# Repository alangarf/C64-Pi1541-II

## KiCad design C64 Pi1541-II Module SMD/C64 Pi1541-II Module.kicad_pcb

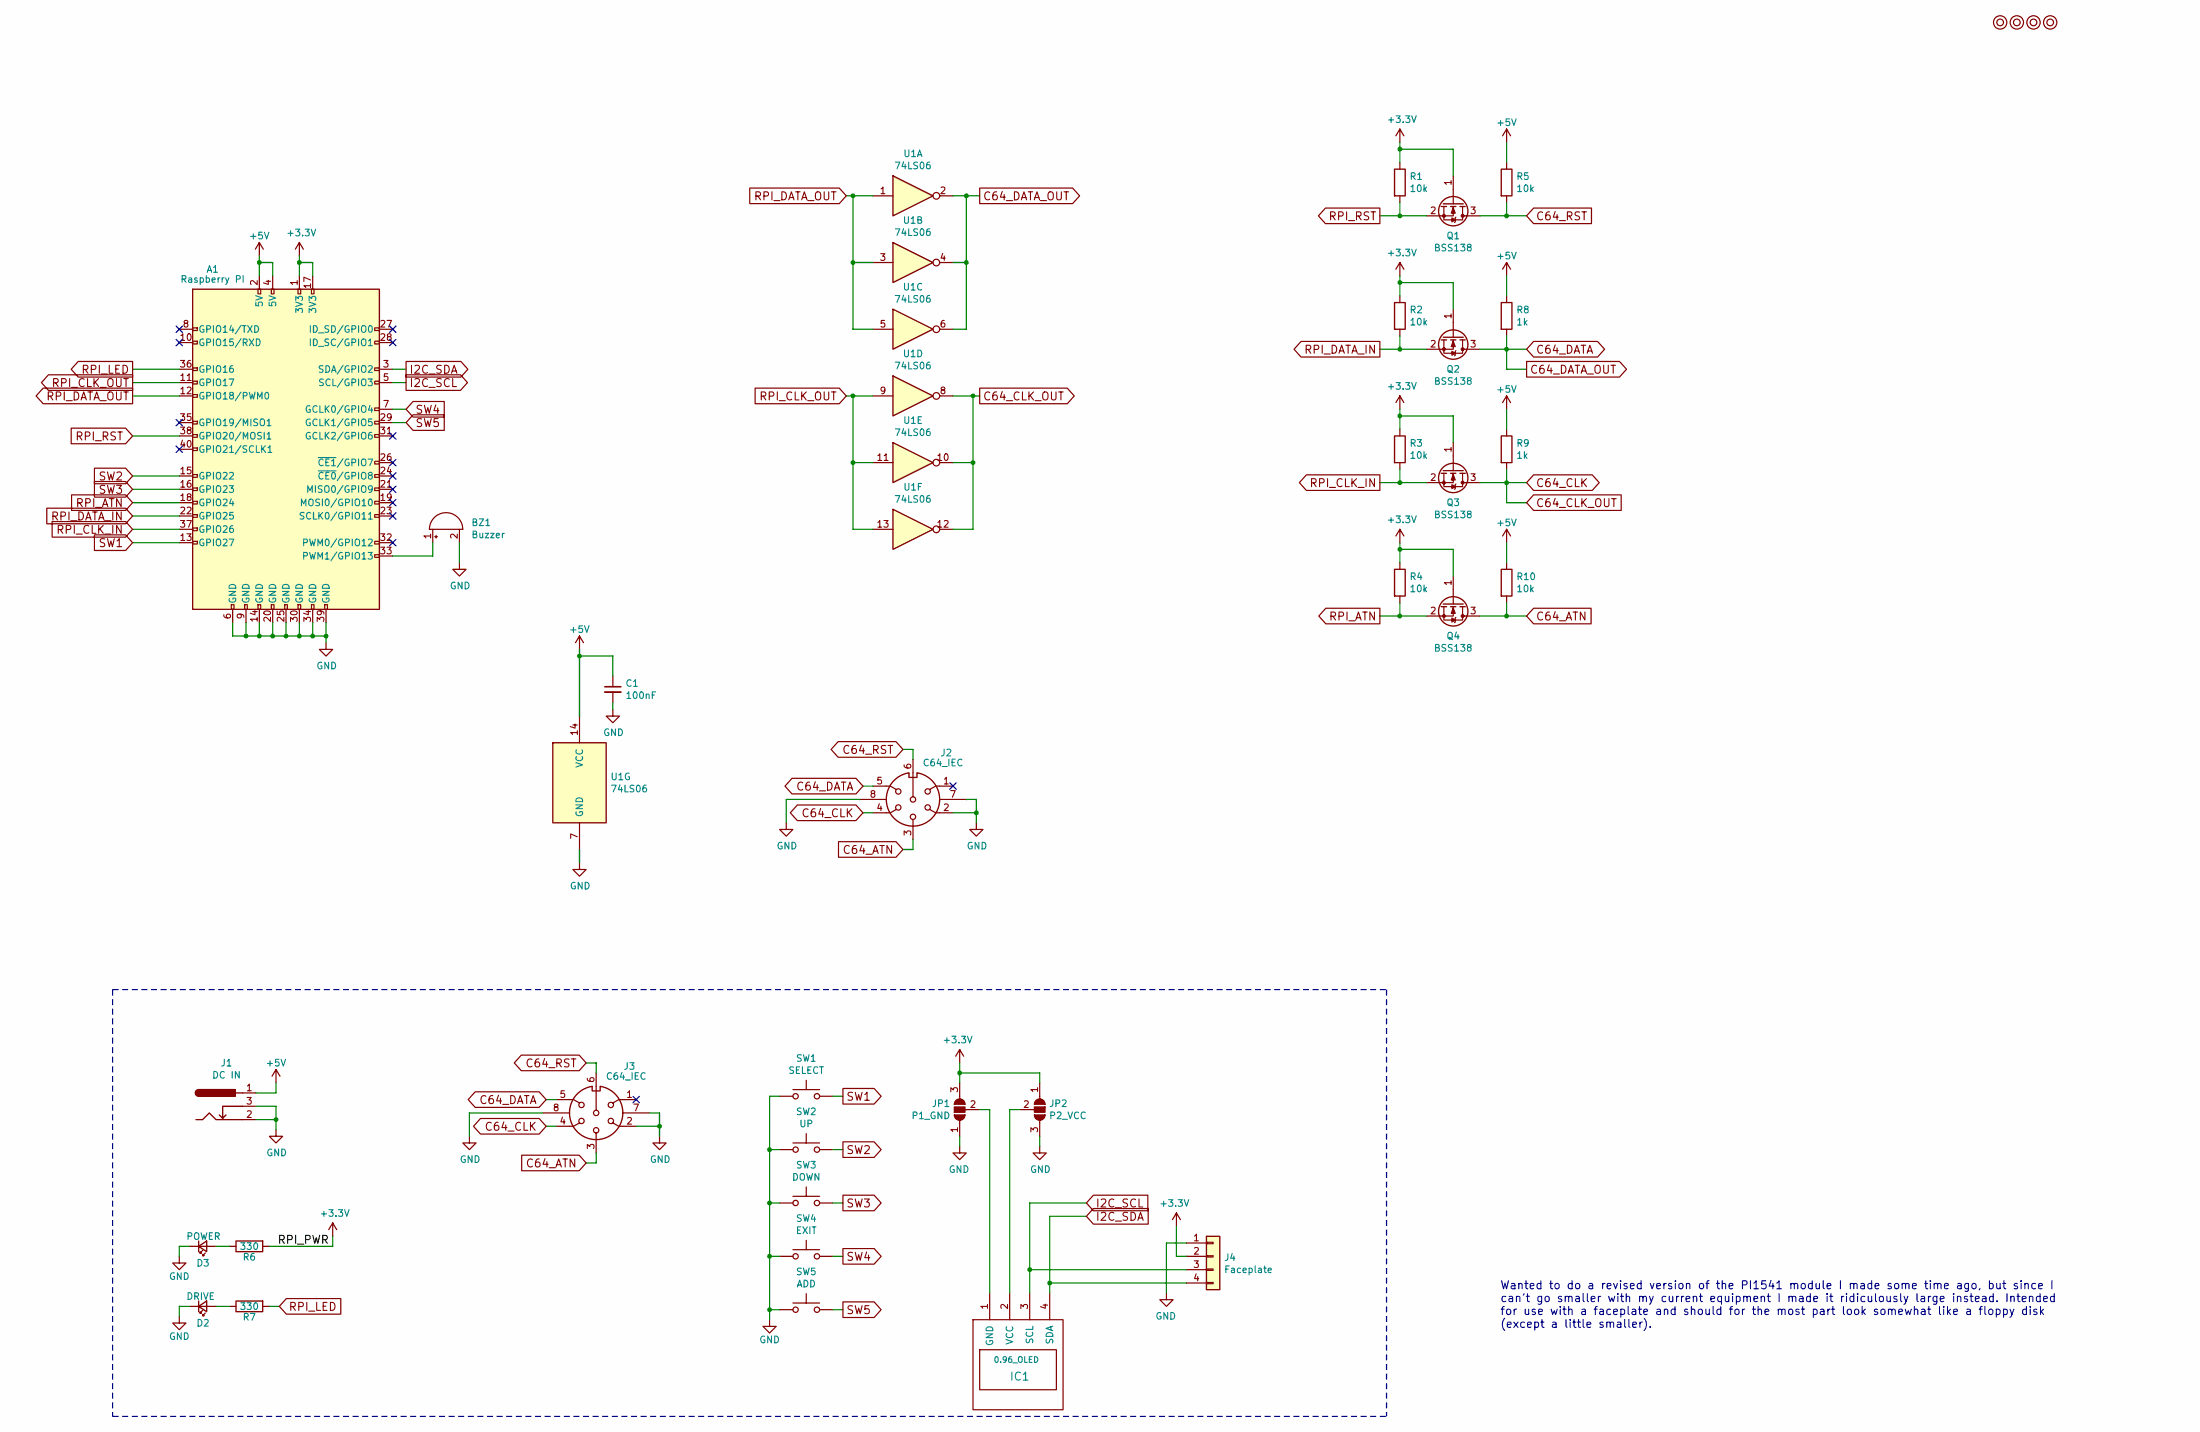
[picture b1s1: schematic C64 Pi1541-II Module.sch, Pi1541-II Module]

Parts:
A1: Raspberry PI; Raspberry_Pi_3B_Socketed_THT_FaceDown_MountingHoles
BZ1: Buzzer; Buzzer_12x9.5RM7.6
C1: 100nF; C_0805_2012Metric_Pad1.18x1.45mm_HandSolder
D2: DRIVE; LED_0805_2012Metric_Pad1.15x1.40mm_HandSolder
D3: POWER; LED_0805_2012Metric_Pad1.15x1.40mm_HandSolder
IC1: 0.96_OLED; 0.96_I2C_OLED
J1: DC IN; BarrelJack_Horizontal
J2, J3: C64_IEC
J4: Faceplate; PinHeader_1x04_P2.54mm_Vertical
JP1: P1_GND; OLED_SEL
JP2: P2_VCC; OLED_SEL
M1, M2, M3, M4: Mounting; M3
Q1, Q2, Q3, Q4: BSS138; SOT-23
R1, R2, R3, R4, R5, R10: 10k; R_0805_2012Metric_Pad1.20x1.40mm_HandSolder
R6, R7: 330; R_0805_2012Metric_Pad1.20x1.40mm_HandSolder
R8, R9: 1k; R_0805_2012Metric_Pad1.20x1.40mm_HandSolder
SW1: SELECT; SW_Tactile_SPST_Angled_PTS645Vx39-2LFS
SW2: UP; SW_Tactile_SPST_Angled_PTS645Vx39-2LFS
SW3: DOWN; SW_Tactile_SPST_Angled_PTS645Vx39-2LFS
SW4: EXIT; SW_Tactile_SPST_Angled_PTS645Vx39-2LFS
SW5: ADD; SW_Tactile_SPST_Angled_PTS645Vx39-2LFS
U1: 74LS06; SOIC-14_3.9x8.7mm_P1.27mm

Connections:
+3V3: A1.1 (3V3), A1.17 (3V3), J4.2, JP1.3 (B), JP2.1 (A), Q1.1 (G), Q2.1 (G), Q3.1 (G), Q4.1 (G), R1.1, R2.1, R3.1, R4.1, R6.2
+5V: A1.2 (5V), A1.4 (5V), C1.1, J1.1, R5.1, R8.1, R9.1, R10.1, U1.14 (VCC)
C64_ATN: J2.3, J3.3, Q4.3 (D), R10.2
C64_CLK: J2.4, J3.4, Q3.3 (D), R9.2, U1.8, U1.10, U1.12
C64_DATA: J2.5, J3.5, Q2.3 (D), R8.2, U1.2, U1.4, U1.6
C64_RST: J2.6, J3.6, Q1.3 (D), R5.2
GND: A1.6 (GND), A1.9 (GND), A1.14 (GND), A1.20 (GND), A1.25 (GND), A1.30 (GND), A1.34 (GND), A1.39 (GND), BZ1.2 (+), C1.2, D2.1 (K), D3.1 (K), J1.2, J1.3, J2.2, J2.7, J2.8, J3.2, J3.7, J3.8, J4.1, JP1.1 (A), JP2.3 (B), SW1.1, SW2.1, SW3.1, SW4.1, SW5.1, U1.7 (GND)
I2C_SCL: A1.5 (SCL/GPIO3), IC1.3 (SCL), J4.3
I2C_SDA: A1.3 (SDA/GPIO2), IC1.4 (SDA), J4.4
unnamed: A1.33 (PWM1/GPIO13), BZ1.1 (-)
unnamed: D2.2 (A), R7.1
unnamed: D3.2 (A), R6.1
unnamed: IC1.1 (GND), JP1.2 (C)
unnamed: IC1.2 (VCC), JP2.2 (C)
RPI_ATN: A1.18 (GPIO24), Q4.2 (S), R4.2
RPI_CLK_IN: A1.37 (GPIO26), Q3.2 (S), R3.2
RPI_CLK_OUT: A1.11 (GPIO17), U1.9, U1.11, U1.13
RPI_DATA_IN: A1.22 (GPIO25), Q2.2 (S), R2.2
RPI_DATA_OUT: A1.12 (GPIO18/PWM0), U1.1, U1.3, U1.5
RPI_LED: A1.36 (GPIO16), R7.2
RPI_RST: A1.38 (GPIO20/MOSI1), Q1.2 (S), R1.2
SW1: A1.13 (GPIO27), SW1.2
SW2: A1.15 (GPIO22), SW2.2
SW3: A1.16 (GPIO23), SW3.2
SW4: A1.7 (GCLK0/GPIO4), SW4.2
SW5: A1.29 (GCLK1/GPIO5), SW5.2

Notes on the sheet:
Wanted to do a revised version of the PI1541 module I made some time ago, but since I can't go smaller with my current equipment I made it ridiculously large instead. Intended for use with a faceplate and should for the most part look somewhat like a floppy disk (except a little smaller).

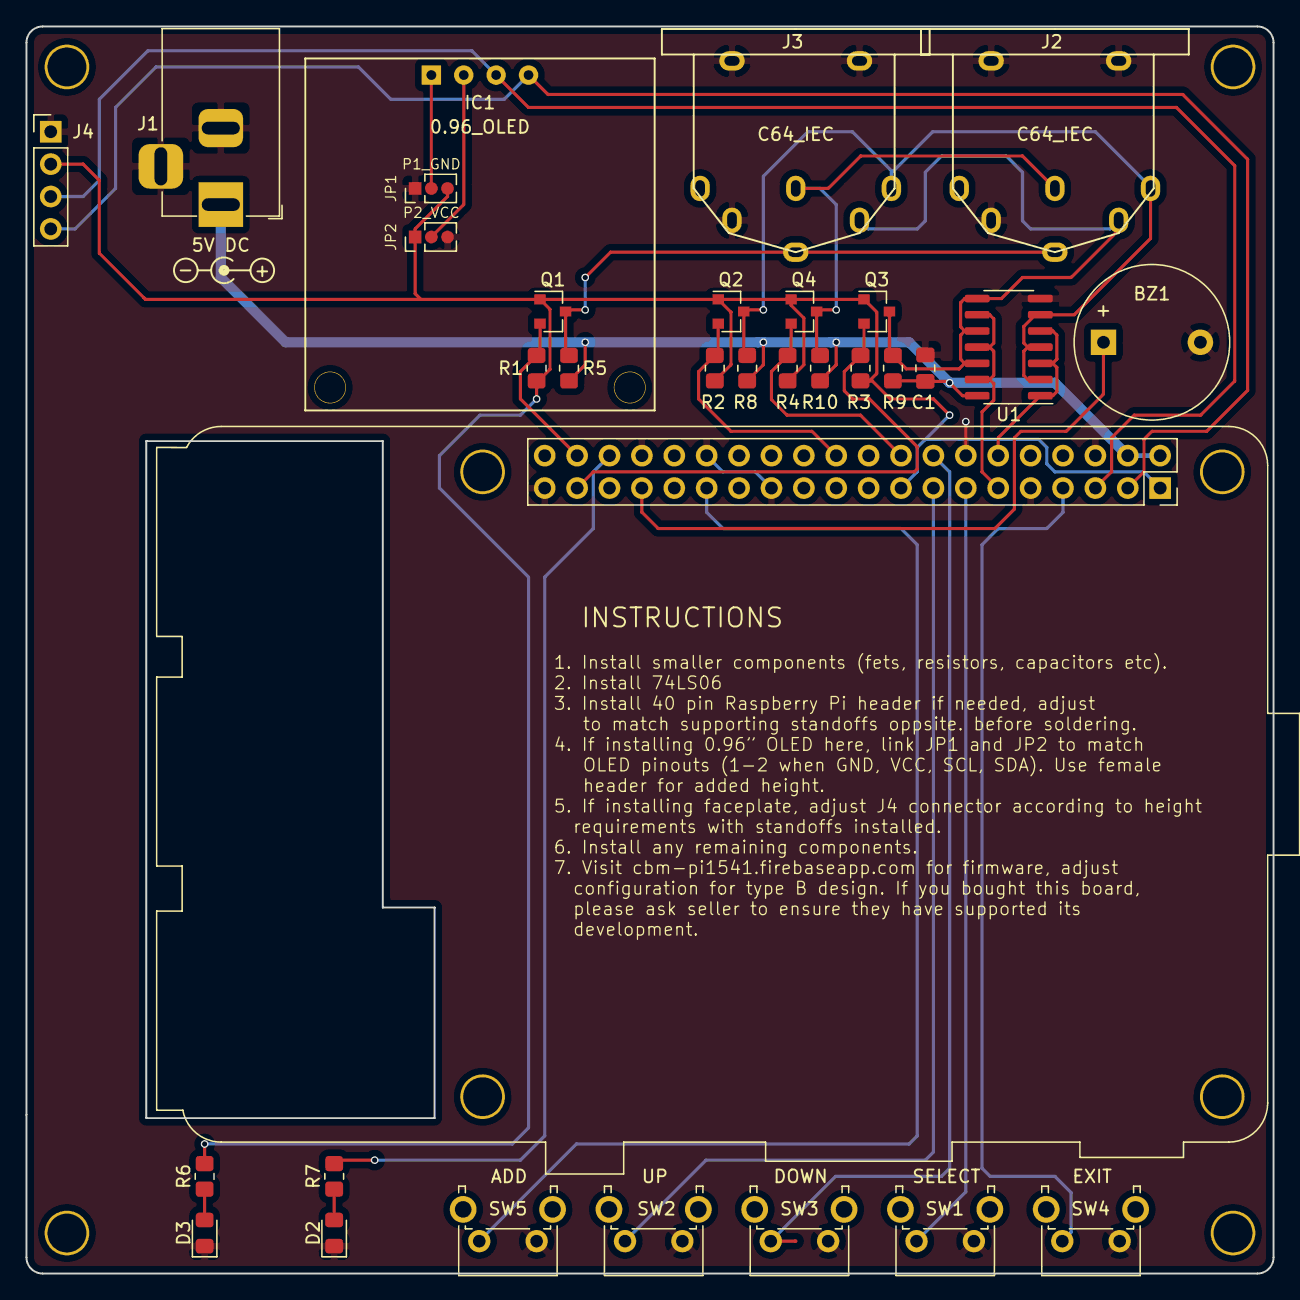
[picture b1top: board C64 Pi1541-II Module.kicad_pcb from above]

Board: 2 copper layers, 97.8 x 97.8 mm, 36 parts (0 on the bottom side), 26 nets.

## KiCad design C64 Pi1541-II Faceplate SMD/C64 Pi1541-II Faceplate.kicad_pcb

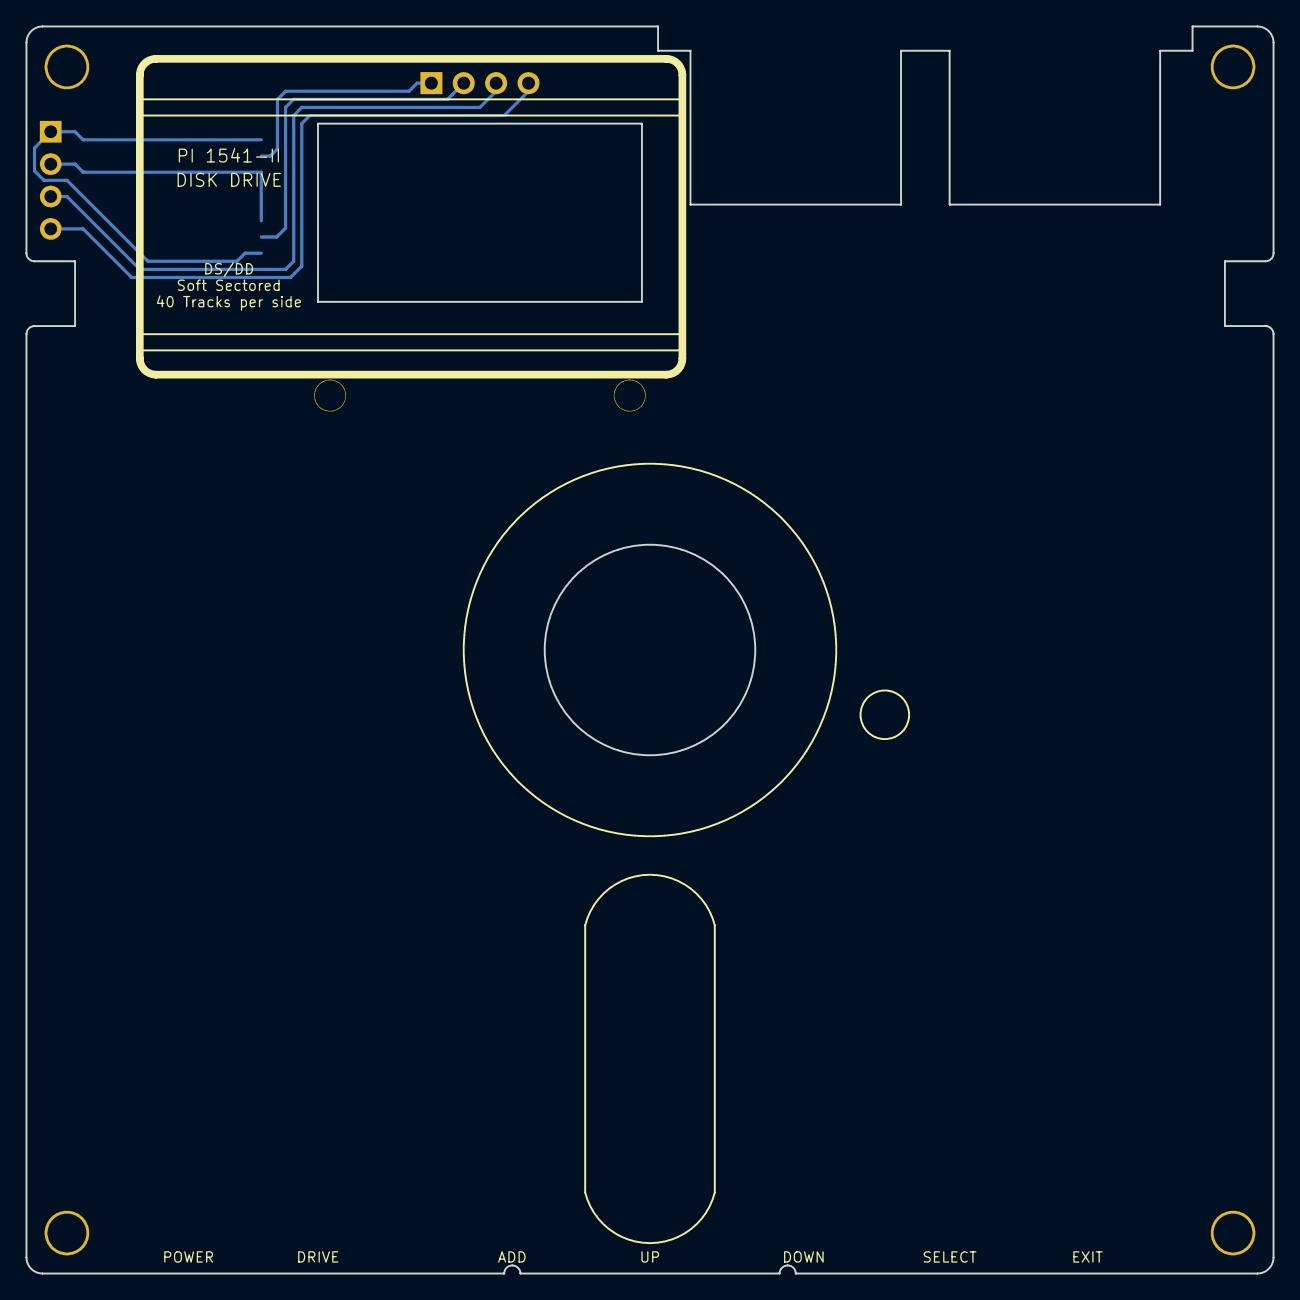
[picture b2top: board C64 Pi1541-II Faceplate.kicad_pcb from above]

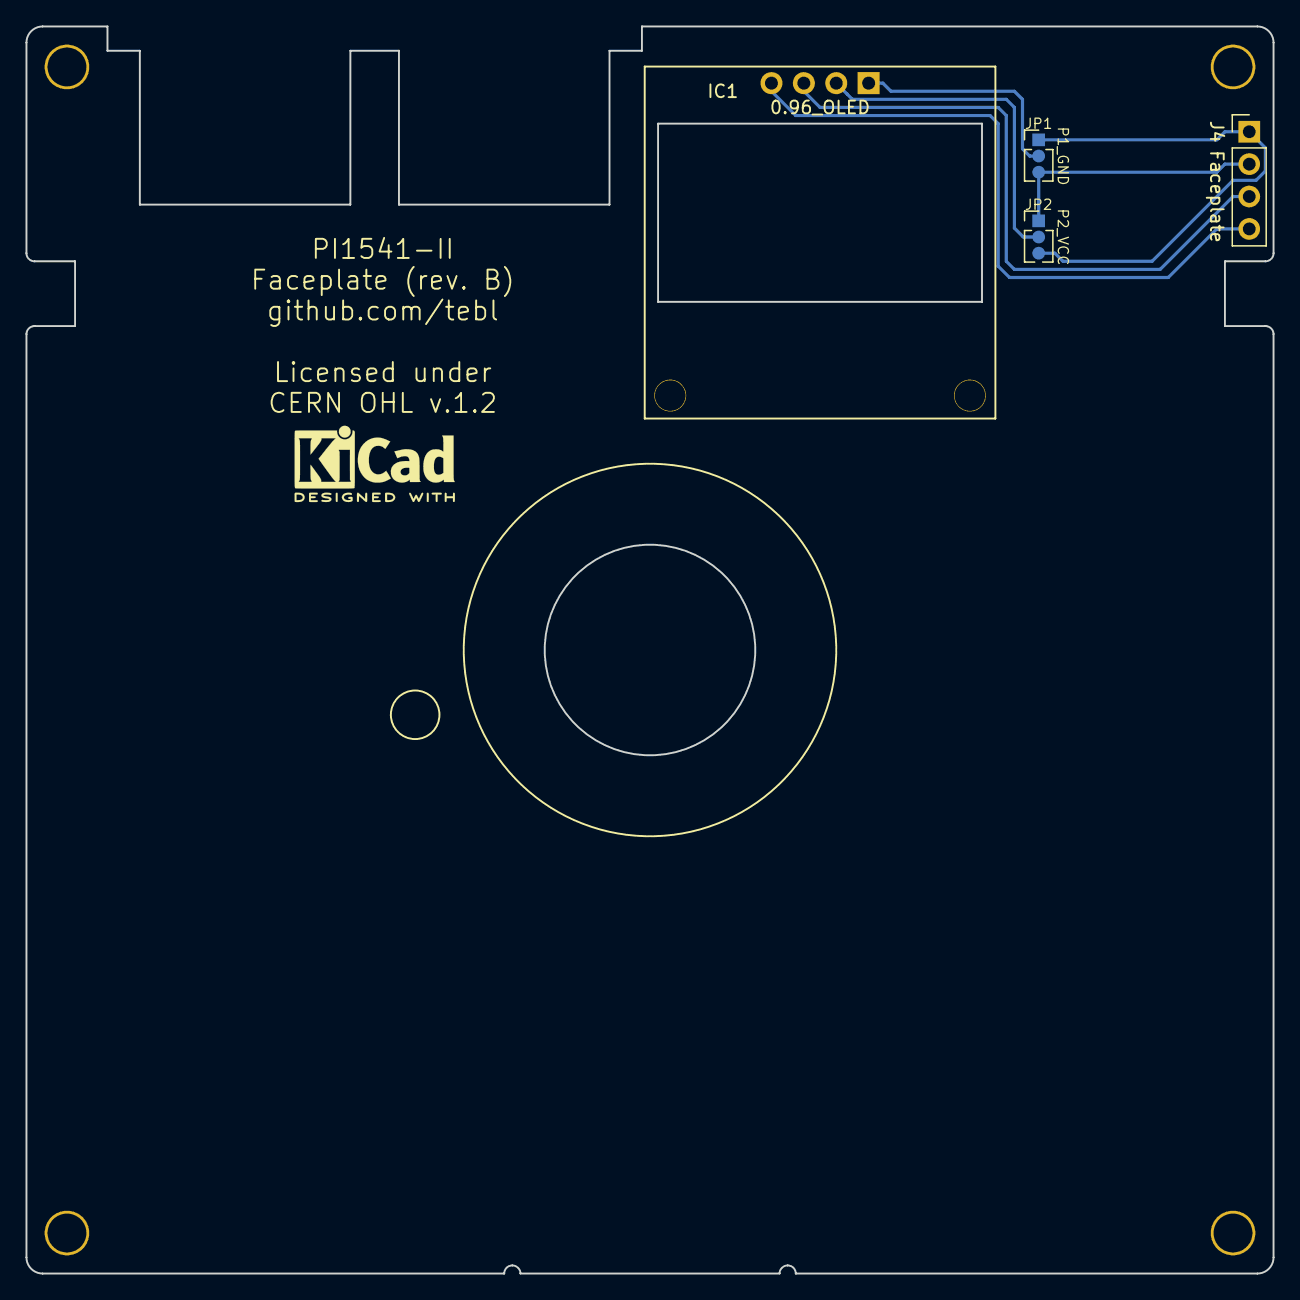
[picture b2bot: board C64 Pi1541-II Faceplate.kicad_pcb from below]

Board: 2 copper layers, 97.8 x 97.8 mm, 8 parts (3 on the bottom side), 6 nets.

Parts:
IC1: 0.96_OLED; 0.96_I2C_OLED2
J4: Faceplate; Pin_Header_Straight_1x04_Pitch2.54mm
JP1: P1_GND; OLED_SEL
JP2: P2_VCC; OLED_SEL
M1, M2, M3, M4: Mounting; M3

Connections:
+3V3: J4.2, JP1.3, JP2.1
GND: J4.1, JP1.1, JP2.3
I2C_SCL: IC1.3, J4.3
I2C_SDA: IC1.4, J4.4
unnamed: IC1.1, JP1.2
unnamed: IC1.2, JP2.2

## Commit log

2020-11-29 Added SMD version of Module and a matching Faceplate

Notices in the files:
C64 Pi1541-II Faceplate SMD/C64 Pi1541-II Faceplate.kicad_pcb:
Licensed under
CERN OHL v.1.2
